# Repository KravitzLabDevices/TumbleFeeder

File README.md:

# TumbleFeeder
This is a feeding device for mice

## Front 

## Back

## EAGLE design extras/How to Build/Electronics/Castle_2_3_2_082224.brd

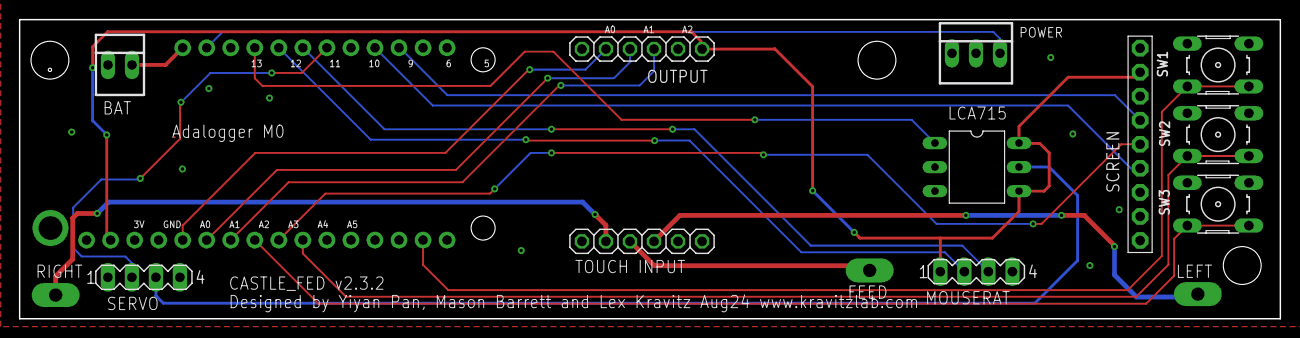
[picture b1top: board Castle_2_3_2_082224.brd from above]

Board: 2 copper layers, 133.2 x 31.6 mm, 15 parts (0 on the bottom side), 21 nets.

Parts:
EXTRAGND, EXTRAGND1, EXTRAGND2: 1X1-BIGPOGO
LCA715: LCA715S; LCA7XX
MOUSERAT: MA04-1
MS2: FEATHERWING_NODIM; FEATHERWING_DIM
OUTPUT: 1X06
POWER: 22-23-2031
SCREEN: 1X09-BIG
SERVO: MA04-1
SW1, SW2, SW3: B3F-10XX
TOUCH_INPUT: 1X06
X1: 22-23-2021

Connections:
1: MS2.15, SW1.3, SW1.4
3V: LCA715.P$4, LCA715.P$6, MOUSERAT.1, MS2.2, OUTPUT.1, SCREEN.8
5: MS2.19, SCREEN.6
6: MS2.20, SCREEN.4
10: MS2.22, SERVO.2
11: MOUSERAT.3, MS2.23
12: MOUSERAT.2, MS2.24
13: LCA715.P$1, MS2.25
A0: MS2.5, OUTPUT.5
A1: MS2.6, OUTPUT.4
A2: MS2.7, OUTPUT.3
A3: MS2.8, SW3.3, SW3.4
A4: MS2.9, SCREEN.5
A5: MS2.10, SW2.3, SW2.4
EN: MS2.27, POWER.3
GND: LCA715.P$2, MOUSERAT.4, MS2.4, MS2.16, POWER.1, POWER.2, SCREEN.7, SERVO.4, SW1.1, SW1.2, SW2.1, SW2.2, SW3.1, SW3.2, TOUCH_INPUT.1, X1.1
SERVO_POWER: LCA715.P$5, SERVO.3
TOUCH1: EXTRAGND.P$1, TOUCH_INPUT.3
TOUCH2: EXTRAGND1.P$1, TOUCH_INPUT.4
TOUCH3: EXTRAGND2.P$1, TOUCH_INPUT.5
VBAT: MS2.28, X1.2

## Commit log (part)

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2022-06-22 yy commit from local folder
2022-06-23 yy commit
2022-06-24 yy commit library
2022-06-24 Update README.md
    yy just updated to her branch but hasn't merge branch yet
2022-07-27 message
2022-10-10 delete sleep
    delete sleep
2022-10-14 20s_to_60s
    open time for feeding changed from 20s to 60s
2022-11-19 free feeding move added
2022-11-25 update_input
2022-12-28 added eInk code
    Added variant of the code for eInk screen
2023-01-06 screen change
2023-01-11 need to fix screen
2023-01-13 screen fixed
2023-01-13 added lowpower wakeup. works perfectly. need to test power consumption
2023-01-17 comments added
2023-01-27 MOSFET ON PIN 11
    power consumption under sleep mode ~ 0.58 mA
2023-04-12 updated
    updated
2023-05-29 version 2.1
2023-06-05 version2.3
2023-06-09 freefeed lowpower fixed
2023-06-23 button left right updated
2023-06-26 rtc time
2023-07-10 lastest
2023-07-18 Added a pulse
2023-08-15 Organized code
2023-08-16 Updated Menu
2023-08-17 Uploaded YY data
2023-09-05 edited out triggered video
2023-09-21 updated menu display
2023-09-24 added beeper
2023-10-12 More Example Data
2023-11-16 Fixed bug related to FR1 vs Free
2024-01-30 Shake and Low Power
    Got ride of shake subtraction and restarted low power mode
2024-02-01 updated electronics
2024-02-01 removed delay from main loop
2024-02-01 fixed bug
2024-06-04 New Castle Pictures
2024-07-25 added FR customization
2024-07-26 added zip for v2
2024-07-26 update v2
2024-07-29 updated FR bug
2024-11-15 Added Device number to CSV and fixed blank file bug
2024-11-21 Fixed issue where touch durations were not being recorded
2025-02-27 Organizing
2025-08-04 Uploaded how to build video
2025-08-13 MiniTumbler 3D file
2025-08-13 MiniTumbler Code (Needs to be tested)
2025-09-03 Updated STLs
2025-09-03 Remove 3D_Design assets and documentation
    Deleted Castle.png and readme.md from the 3D_Design directory. These files are no longer needed in the project.
2025-09-03 Restructure and relocate project files
    Moved code, 3D files, and electronics design files into a new organized directory structure under 'How to Build', including AlternateDesigns, OldVersions, and TumblerFeederCode. Deleted CastleCodev2.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
2025-09-03 Removed old code
2025-09-03 Reorg exampleData
2025-09-03 Reorganized Data
2025-09-04 Added Photos
2025-09-04 Moved photos
2025-10-16 Started Prox Variant
2025-10-16 Integrate VL6180X proximity sensor for feeder detection
    Added VL6180X sensor initialization and reading logic to detect proximity of mice to the feeder. Introduced checkProx.ino to handle sensor readings and set left_touch accordingly. Updated main loop t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
2025-10-17 Refactor for proximity-based feeder mode and UI updates
    Reworked input checking logic to support proximity-based (Prox) mode, removing right poke checks and simplifying left poke handling. Updated display labels from 'FR' to 'Prox' and 'ProxTime' for clar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
2025-10-17 Refactor input logic to use proximity detection
    Replaces left/right touch logic with mouse proximity detection throughout the codebase. Updates variable names, display output, and data logging to reflect 'Approach' and 'Feed' events. Removes unuse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
2025-10-17 Add detailed comments and improve UI in feeder code
    Extensive documentation and comments were added to Checkinputs.ino and Display.ino, clarifying input handling, feeding logic, and user interface flow. The display menus now include more descriptive l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
2025-10-17 Rename FeederCount to OpenCount throughout codebase
    Replaces all instances of the FeederCount variable with OpenCount for clarity and consistency in event tracking. Updates variable usage, display output, CSV logging, and documentation comments to ref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
2025-10-17 Move ProxTumbler feeder code to new directory
    Renamed and relocated all TumblerFeederCode_Prox source files from AlternateDesigns/TumblerFeederCode_Prox to AlternateDesigns/ProxTumbler/TumblerFeederCode_Prox for improved organization and clarity.
2025-10-17 Remove description of ProxTumbler design
2025-10-17 Revise readme for ProxTumbler variant
    Updated the readme to introduce the ProxTumbler variant and provide a concise overview of the build process, including links to resources and detailed steps.
2025-10-17 Update image in ProxTumbler readme
2026-03-02 Added library files
2026-03-02 Edited library format
2026-03-13 Added new tasks
2026-03-13 Rename
2026-03-13 Format Changes
2026-04-07 Screen not updating during Free termination
2026-04-07 Fixed flashing timer on FreeTerm
2026-04-10 Added new events for FreeTerm task
2026-04-13 Added proxfeeder as a standalone task and the 5th task in the classic tumble feeder sketch
2026-04-13 Updated Prox task screen display
2026-04-17 Fixed naming error from "2_"
2026-05-23 Increased prox open duration settings
2026-06-02 Removed folder
2026-06-05 Bump version to 2.2.0
